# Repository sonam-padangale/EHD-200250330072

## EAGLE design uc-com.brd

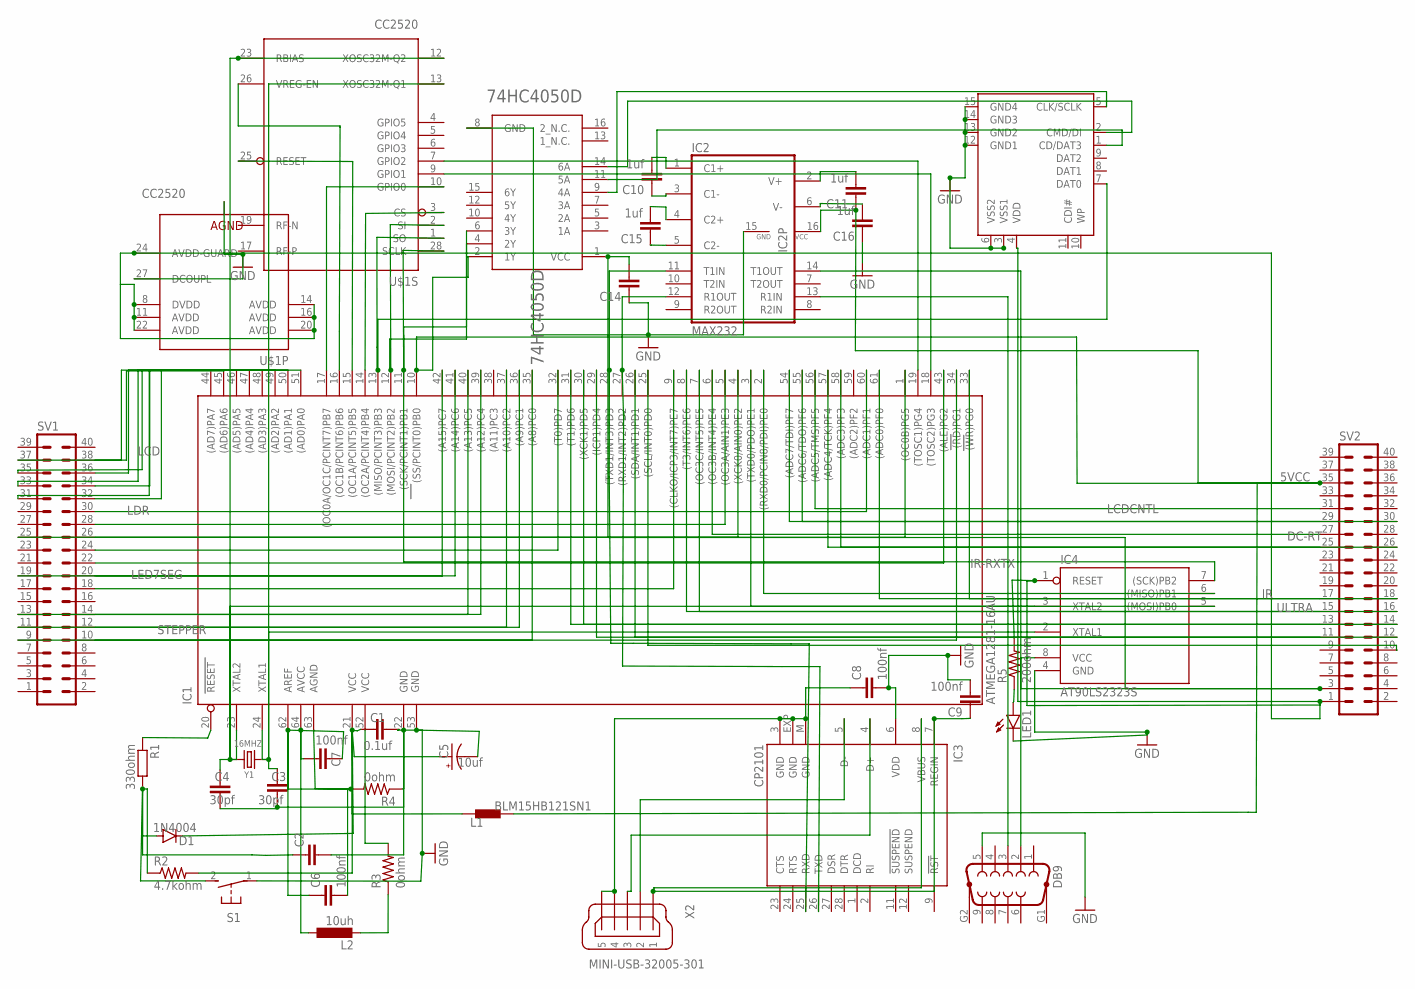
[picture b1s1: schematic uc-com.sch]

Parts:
74HC4050D: NXP_74HC4050DNXP_74HC4050D_0_0; NXP_74HC4050D_0
C1: 0.1uf; C0201
C2: C-EUC0402; C0402
C3, C4: 30pf; C0201
C5: 10uf; 085CS_1AR
C6, C7, C8, C9: 100nf; C0402K
C10, C11, C15, C16: 1uf; C0402K
C14: C-EUC0402K; C0402K
D1: 1N4004; DO41-10
DB9: F09HP-7.2
IC1: ATMEGA1281-16AU; TQFP64
IC2: MAX232; DIL16
IC3: CP2101; MLP28
IC4: AT90LS2323S; SO08
L1: BLM15HB121SN1; 0402
L2: 10uh; 0204/7
LED1: LED5MM
R1: 330ohm; R0603
R2: 4.7kohm; M0805
R3, R4: 0ohm; M0805
R5: 200ohm; M0805
S1: 31-XX; B3F-31XX
SDCARD: SDCARDVAR2; SDCMF-10915W010
SV1, SV2: 40P
U$1: CC2520; QFN50P500X500X100-29N
X2: MINI-USB-32005-301; 32005-301
Y1: 16MHZ; HC49US

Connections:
5VCC: 74HC4050D.2 (1Y), C11.1, IC1.10 ((SS/PCINT0)PB0), IC2.16 (VCC), L1.1, SV2.35
7SEG: IC1.41 ((A14)PC6), SV1.19
DC-RT: IC1.6 ((OC3B/INT4)PE4), SV2.27
DH: IC1.32 ((T0)PD7), SV1.24
GND: 74HC4050D.8 (GND), C1.2, C2.2, C3.2, C4.2, C5.-, C8.2, C9.2, C14.1, C16.1, DB9.5, IC1.22 (GND), IC1.53 (GND1), IC2.15 (GND), IC3.6 (VDD), IC4.4 (GND), LED1.K (C), R4.1, S1.1, SDCARD.3 (VSS1), SDCARD.6 (VSS2), SDCARD.12 (GND1), SDCARD.13 (GND2), SDCARD.14 (GND3), SDCARD.15 (GND4), U$1.27 (DCOUPL), U$1.29 (AGND)
IR: IC1.61 ((ADC0)PF0), SV2.17
IR-RXTX: IC1.33 ((WR)PG0), SV2.18
LCD: IC1.45 ((AD6)PA6), SV1.37
LCDCNTL: IC1.56 ((ADC5/TMS)PF5), SV2.31
LDR: IC1.60 ((ADC1)PF1), SV1.30
LED7SEG: IC1.43 ((ALE)PG2), SV1.22
unnamed: C2.1, D1.A, R1.2, R2.1, S1.2 (S)
unnamed: IC1.20 (RESET), R1.1
unnamed: C1.1, C5.+, D1.C, IC1.21 (VCC), L1.2, R2.2
unnamed: 74HC4050D.1 (VCC), C14.2, IC4.8 (VCC), SV2.3
unnamed: C4.1, IC1.23 (XTAL2), IC4.3 (XTAL2), U$1.12 (XOSC32M-Q2), U$1.23 (RBIAS), Y1.2
unnamed: C7.2, IC1.64 (AVCC), L2.1
unnamed: C3.1, IC1.24 (XTAL1), IC4.2 (XTAL1), U$1.13 (XOSC32M-Q1), Y1.1
unnamed: C6.1, C6.2, C7.1, IC1.62 (AREF), IC1.63 (AGND), R4.2
unnamed: IC1.27 ((RXD1/INT2)PD2), IC2.12 (R1OUT), IC3.26 (TXD)
unnamed: L2.2, R3.1
unnamed: IC1.52 (VCC1), R3.2
unnamed: IC1.28 ((TXD1/INT3)PD3), IC2.11 (T1IN), IC3.25 (RXD)
unnamed: IC1.44 ((AD7)PA7), SV1.38
unnamed: IC4.1 (RESET), R5.2, SDCARD.4 (VDD), SV2.1, U$1.8 (DVDD), U$1.11 (AVDD), U$1.14 (AVDD), U$1.16 (AVDD), U$1.20 (AVDD), U$1.22 (AVDD), U$1.24 (AVDD-GUARD)
unnamed: IC1.46 ((AD5)PA5), SV1.36
unnamed: IC1.47 ((AD4)PA4), SV1.35
unnamed: IC1.48 ((AD3)PA3), SV1.34
unnamed: IC1.49 ((AD2)PA2), SV1.33
unnamed: IC1.50 ((AD1)PA1), SV1.32
unnamed: IC1.51 ((AD0)PA0), SV1.31
unnamed: IC1.15 ((OC1A/PCINT5)PB5), U$1.25 (RESET)
unnamed: IC1.16 ((OC1B/PCINT6)PB6), U$1.26 (VREG-EN)
unnamed: 74HC4050D.6 (3Y), IC1.12 ((MOSI/PCINT2)PB2), U$1.2 (SI)
unnamed: IC1.13 ((MISO/PCINT3)PB3), SDCARD.7 (DAT0), U$1.1 (SO)
unnamed: 74HC4050D.4 (2Y), IC1.11 ((SCK/PCINT1)PB1), IC4.7 ((SCK)PB2), U$1.28 (SCLK)
unnamed: IC1.14 ((OC2A/PCINT4)PB4), U$1.3 (CS)
unnamed: IC1.17 ((OC0A/OC1C/PCINT7)PB7), U$1.10 (GPIO0)
unnamed: IC1.18 ((TOSC2)PG3), U$1.9 (GPIO1)
unnamed: IC1.19 ((TOSC1)PG4), U$1.7 (GPIO2)
unnamed: IC3.5 (D-), X2.2
unnamed: IC3.4 (D+), X2.3
unnamed: C9.1, IC3.7 (REGIN), IC3.8 (VBUS), X2.1
unnamed: C8.1, IC3.3 (GND), IC3.EXP (GND), IC3.M (GND), X2.4, X2.5
unnamed: DB9.3, IC2.13 (R1IN)
unnamed: DB9.2, IC2.14 (T1OUT)
unnamed: C15.1, IC2.5 (C2-)
unnamed: C15.2, IC2.4 (C2+)
unnamed: C11.2, IC2.2 (V+)
unnamed: C10.1, IC2.3 (C1-)
unnamed: C16.2, IC2.6 (V-)
unnamed: C10.2, IC2.1 (C1+)
unnamed: 74HC4050D.14 (6A), SDCARD.2 (CMD/DI)
unnamed: IC1.54 ((ADC7/TDI)PF7), SV2.29
unnamed: 74HC4050D.9 (4A), SDCARD.5 (CLK/SCLK)
unnamed: 74HC4050D.11 (5A), SDCARD.1 (CD/DAT3)
unnamed: IC1.55 ((ADC6/TDO)PF6), SV2.30
unnamed: LED1.A, R5.1
unnamed: IC1.42 ((A15)PC7), SV1.20
unnamed: IC1.58 ((ADC3)PF3), SV2.25
unnamed: IC1.57 ((ADC4/TCK)PF4), SV2.26
unnamed: IC1.1 ((OC0B)PG5), SV1.26
unnamed: IC1.4 ((XCK0/AIN0)PE2), SV1.25
unnamed: IC1.5 ((OC3A/AIN1)PE3), SV1.28
unnamed: IC1.7 ((OC3C/INT5)PE5), SV2.15
unnamed: IC1.25 ((SCL/INT0)PD0), SV2.10
unnamed: IC1.26 ((SDA/INT1)PD1), SV2.11
unnamed: IC1.29 ((ICP1)PD4), SV2.12
unnamed: IC1.30 ((XCK1)PD5), SV2.13
unnamed: IC1.31 ((T1)PD6), SV2.14
unnamed: IC1.35 ((A8)PC0), SV1.10
unnamed: IC1.39 ((A12)PC4), SV1.14
unnamed: IC1.36 ((A9)PC1), SV1.12
unnamed: IC1.37 ((A10)PC2), SV1.11
unnamed: IC1.40 ((A13)PC5), SV1.13
unnamed: IC1.9 ((CLKO/ICP3/INT7)PE7), SV1.18
unnamed: IC1.2 ((RXD0/PCIN8/PDI)PE0), IC4.6 ((MISO)PB1)
unnamed: IC1.3 ((TXD0/PDO)PE1), IC4.5 ((MOSI)PB0)
STEPPER: IC1.34 ((RD)PG1), SV1.9
ULTRA: IC1.8 ((T3/INT6)PE6), SV2.16

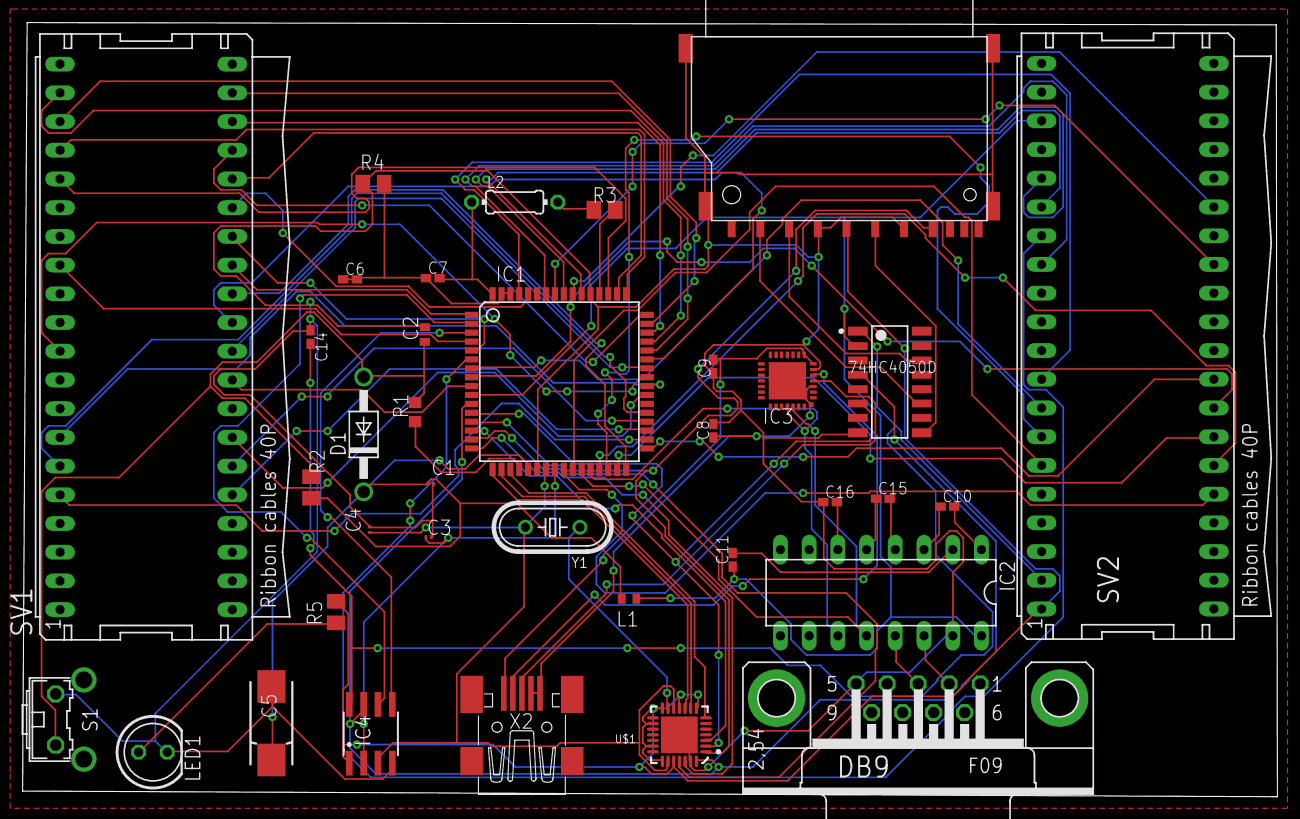
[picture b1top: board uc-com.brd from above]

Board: 2 copper layers, 111.0 x 68.5 mm, 36 parts (0 on the bottom side), 80 nets.

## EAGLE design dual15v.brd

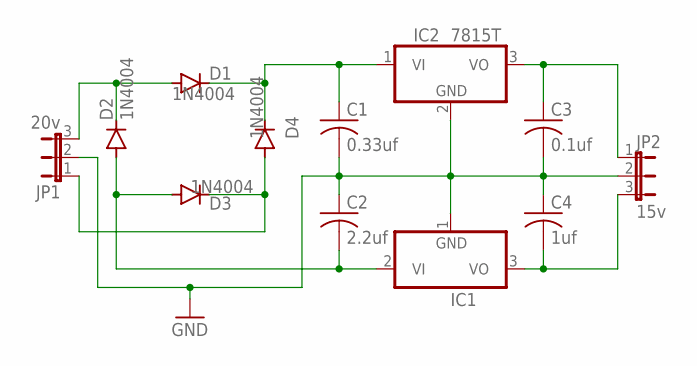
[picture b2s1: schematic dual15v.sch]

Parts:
C1: 0.33uf; C025-025X050
C2: 2.2uf; C025-025X050
C3: 0.1uf; C025-025X050
C4: 1uf; C025-025X050
D1, D2, D3, D4: 1N4004; DO41-10
IC1: 7915T; TO220H
IC2: 7815T; TO220H
JP1: 20v; JP2
JP2: 15v; JP2

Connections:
GND: C1.2, C2.1, C3.2, C4.1, IC1.1 (GND), IC2.2 (GND), JP1.2, JP2.2
unnamed: D1.A, D2.C, JP1.3
unnamed: C2.2, D2.A, D3.A, IC1.2 (VI)
unnamed: D3.C, D4.A, JP1.1
unnamed: C1.1, D1.C, D4.C, IC2.1 (VI)
unnamed: C4.2, IC1.3 (VO), JP2.3
unnamed: C3.1, IC2.3 (VO), JP2.1

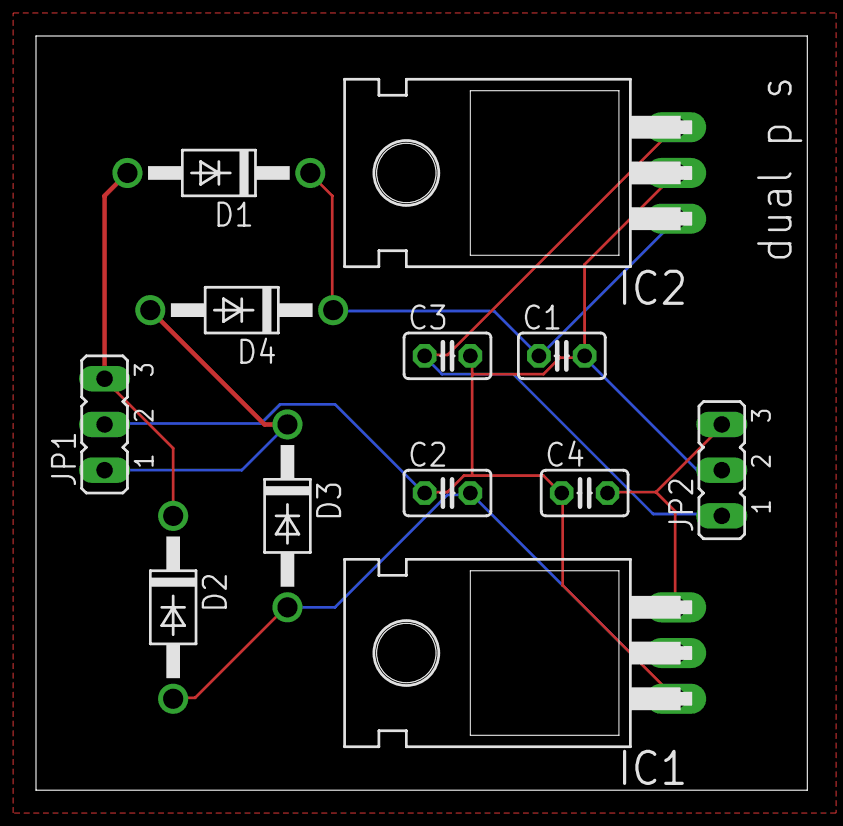
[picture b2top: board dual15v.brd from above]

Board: 2 copper layers, 42.8 x 41.9 mm, 12 parts (0 on the bottom side), 7 nets.

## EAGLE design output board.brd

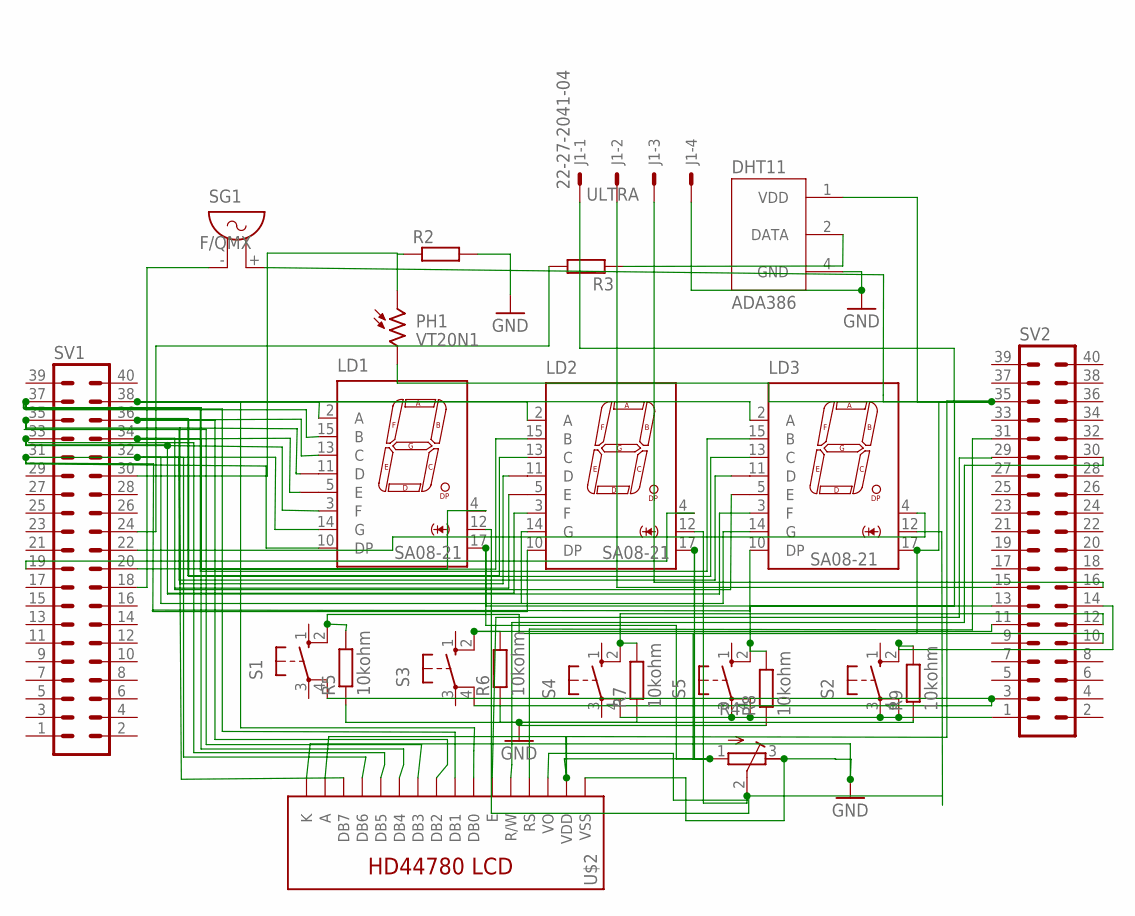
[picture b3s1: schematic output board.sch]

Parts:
DHT11: ADA386; XDCR_ADA386
J1: 22-27-2041-04; 6410-04
LD1, LD2, LD3: SA08-21
PH1: VT20N1; TO46-VT200
R2, R3: R-EU_M0805; M0805
R4: R-TRIMM3224J; RTRIM3224J
R5, R6, R7, R8, R9: 10kohm; R0201
S1, S2, S3, S4, S5: 10-XX; B3F-10XX
SG1: F/QMX
SV1, SV2: 40P
U$2: LCD-HD447803-HOLES16X2-3-HOLES; LCD-16X2-3HOLES

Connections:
GND: DHT11.4 (GND), J1.4, R2.2, R4.3 (E), R5.1, R6.1, R7.1, R8.1, R9.1, U$2.1 (VSS), U$2.16 (K)
unnamed: DHT11.2 (DATA), R3.1
unnamed: LD1.2 (A), LD2.2 (A), LD3.2 (A), SV1.38, U$2.7 (DB0)
unnamed: LD1.15 (B), LD2.15 (B), LD3.15 (B), SV1.37, U$2.8 (DB1)
unnamed: LD1.13 (C), LD2.13 (C), LD3.13 (C), SV1.36, U$2.9 (DB2)
unnamed: LD1.9 (D), LD2.9 (D), LD3.9 (D), SV1.35
unnamed: LD1.7 (E), LD2.7 (E), LD3.7 (E), SV1.34, U$2.11 (DB4)
unnamed: LD1.3 (F), LD2.3 (F), LD3.3 (F), SV1.33
unnamed: LD1.14 (G), LD2.14 (G), LD3.14 (G), SV1.32, U$2.13 (DB6)
unnamed: LD1.10 (DP), LD2.10 (DP), LD3.10 (DP), SV1.31, U$2.14 (DB7)
unnamed: SV2.29, U$2.6 (E)
unnamed: SV2.30, U$2.5 (R/W)
unnamed: SV2.31, U$2.4 (RS)
unnamed: LD1.12 (AN), LD2.12 (AN), LD3.12 (AN), R4.2 (S), U$2.3 (VO)
unnamed: PH1.1, R2.1
unnamed: R5.2, S1.2 (S1), SV2.10
unnamed: R6.2, S3.2 (S1), SV2.11
unnamed: R7.2, S4.2 (S1), SV2.12
unnamed: LD1.4 (AN), SV1.20
unnamed: LD2.4 (AN), SV1.19
unnamed: LD3.4 (AN), SV1.22
unnamed: R8.2, S5.2 (S1), SV2.13
unnamed: R9.2, S2.2 (S1), SV2.14
unnamed: S1.4 (P1), S3.4 (P1), SV2.3
unnamed: S2.3, S2.4 (P1), S4.4 (P1), S5.3, S5.4 (P1), SV2.1
unnamed: R3.2, SV1.24
unnamed: J1.2, SV2.15
unnamed: SG1.- (1), SV1.18
unnamed: J1.3, SV2.16
ULTRA: DHT11.1 (VDD), J1.1, LD1.17 (AN), LD2.17 (AN), LD3.17 (AN), PH1.2, R4.1 (A), SG1.+ (2), SV2.35, U$2.2 (VDD), U$2.15 (A)

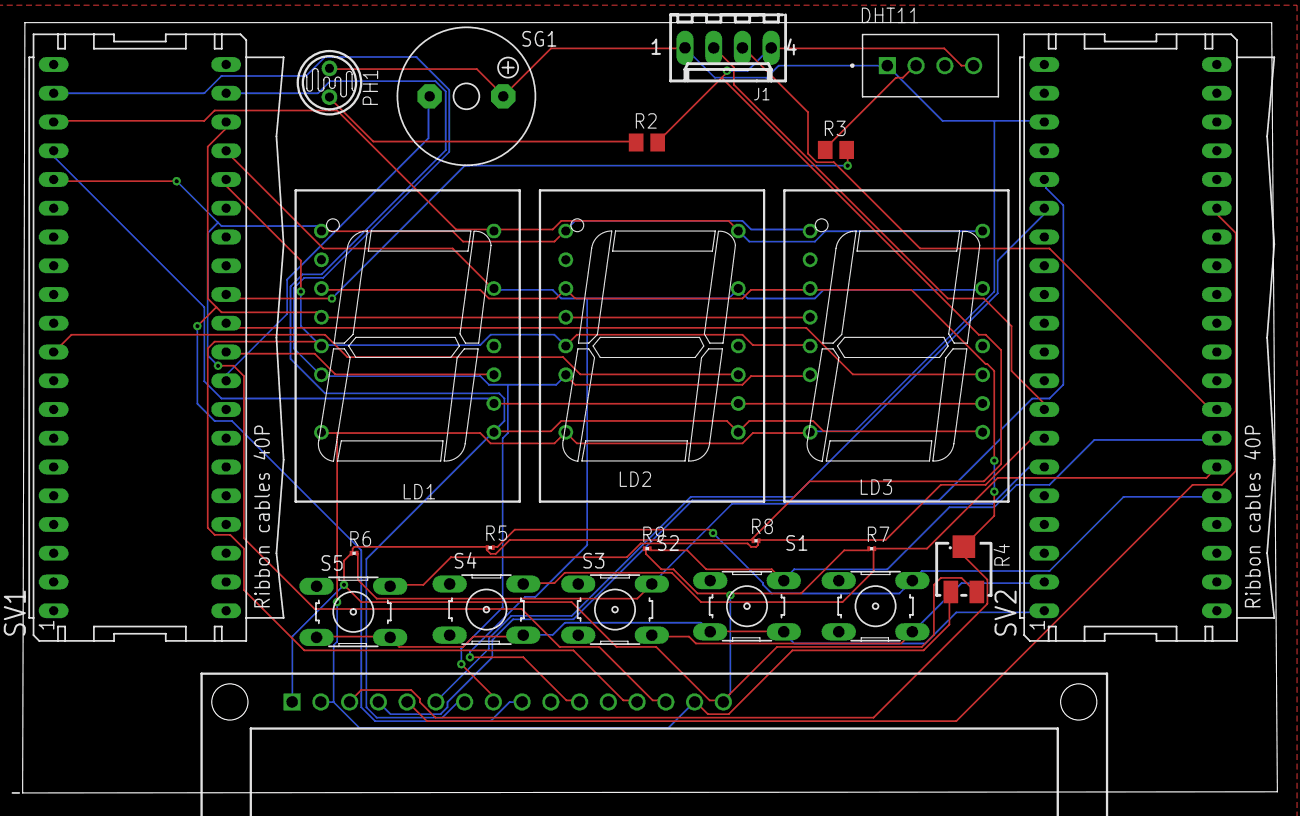
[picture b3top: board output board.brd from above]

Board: 2 copper layers, 110.9 x 68.1 mm, 23 parts (0 on the bottom side), 30 nets.

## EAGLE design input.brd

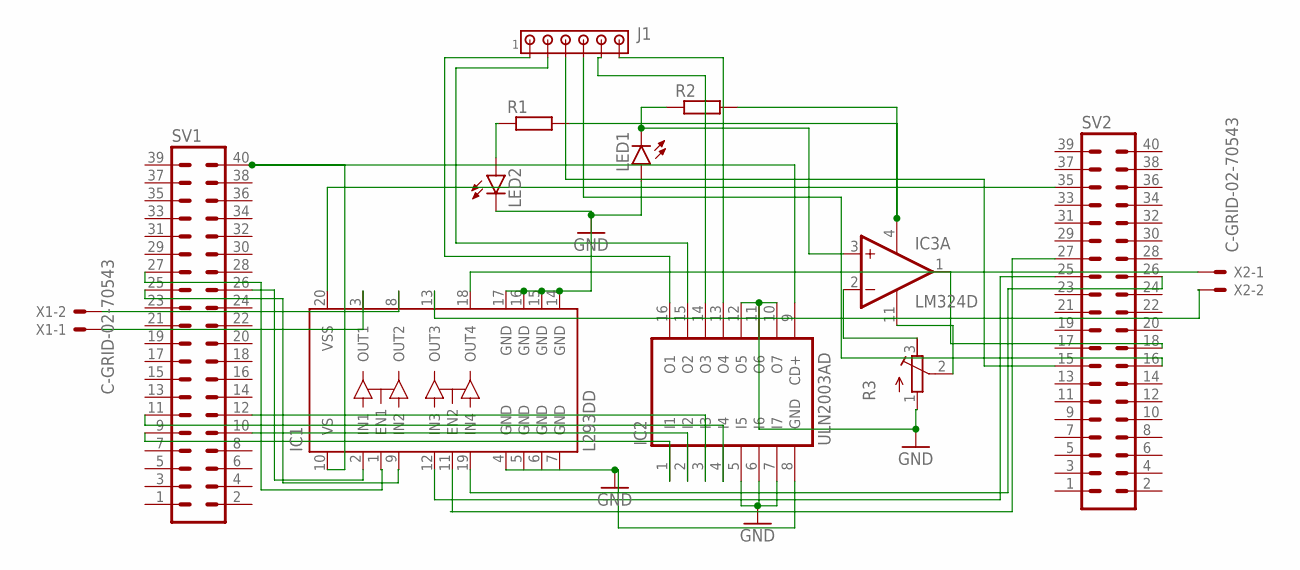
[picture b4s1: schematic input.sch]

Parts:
IC1: L293DD; SO20
IC2: ULN2003AD; SO16
IC3: LM324D; SO14
J1: MTA06-100; 10X06MTA
LED1, LED2: LED5MM
R1, R2: R-EU_R0201; R0201
R3: R-TRIMM3103; RTRIM3103
SV1, SV2: 40P
X1, X2: C-GRID-02-70543; 70543-02

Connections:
GND: IC1.4 (GND), IC1.5 (GND), IC1.6 (GND), IC1.7 (GND), IC1.14 (GND), IC1.15 (GND), IC1.16 (GND), IC1.17 (GND), IC2.5 (I5), IC2.6 (I6), IC2.7 (I7), IC2.8 (GND), IC2.10 (O7), IC2.11 (O6), IC2.12 (O5), LED1.A, LED2.K (C), R3.1 (A)
unnamed: IC3.3 (+IN), LED1.K (C), R2.1
unnamed: LED2.A, R1.1
unnamed: IC3.11 (V-), R3.2 (S)
unnamed: IC3.2 (-IN), R3.3 (E)
unnamed: IC2.1 (I1), SV1.9
unnamed: IC2.2 (I2), SV1.10
unnamed: IC2.3 (I3), SV1.12
unnamed: IC1.2 (IN1), SV1.26
unnamed: IC1.9 (IN2), SV1.25
unnamed: IC1.1 (EN1), SV1.27
unnamed: IC1.12 (IN3), SV2.25
unnamed: IC1.19 (IN4), SV2.26
unnamed: IC1.11 (EN2), SV2.27
unnamed: IC1.3 (OUT1), X1.1
unnamed: IC1.8 (OUT2), X1.2
unnamed: IC1.10 (VS), IC2.9 (CD+), SV1.40
unnamed: IC1.20 (VSS), SV2.35
unnamed: IC2.4 (I4), SV1.11
unnamed: IC1.18 (OUT4), X2.1
unnamed: IC1.13 (OUT3), X2.2
unnamed: IC2.16 (O1), J1.1
unnamed: IC2.15 (O2), J1.2
unnamed: IC2.14 (O3), J1.5
unnamed: IC2.13 (O4), J1.6
unnamed: IC3.4 (V+), R1.2, R2.2
unnamed: IC3.1 (OUT), SV2.18
unnamed: J1.3, SV2.15
unnamed: J1.4, SV2.16

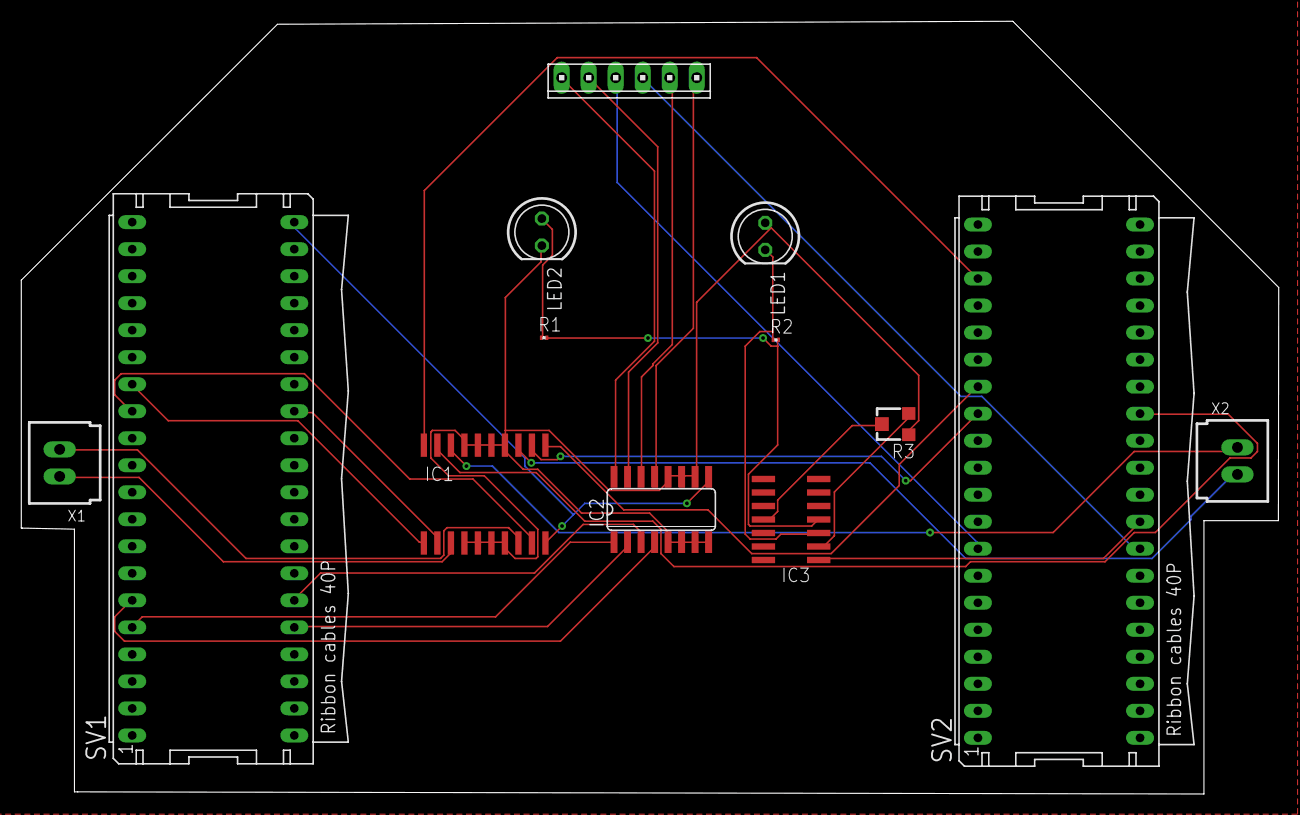
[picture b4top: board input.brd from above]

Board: 2 copper layers, 118.2 x 72.7 mm, 13 parts (0 on the bottom side), 29 nets.

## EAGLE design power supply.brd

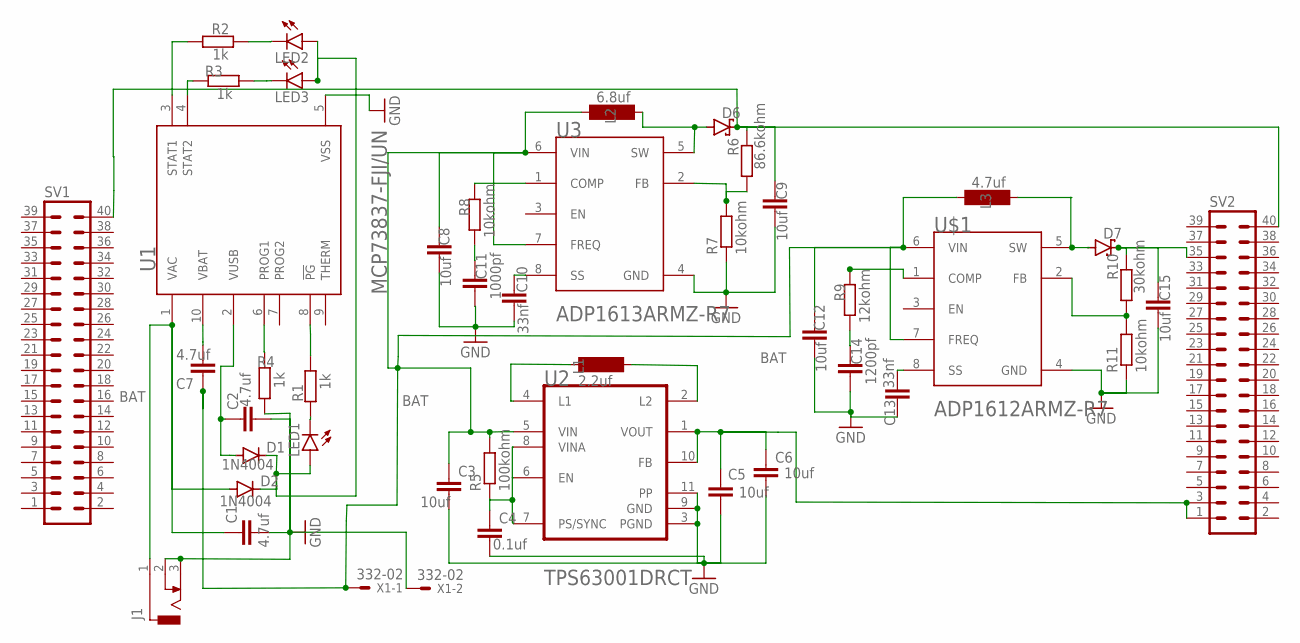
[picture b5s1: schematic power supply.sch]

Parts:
C1, C2, C7: 4.7uf; C025-024X044
C3, C5, C6, C8, C9, C12, C15: 10uf; C0201
C4: 0.1uf; C0201
C10, C13: 33nf; C0201
C11: 1000pf; C0201
C14: 1200pf; C0201
D1, D2: 1N4004; DO41-10
D6, D7: P4KEXX; DO41-10
J1: DCJ0303
L1: 2.2uf; SD75
L2: 6.8uf; SD75
L3: 4.7uf; SD75
LED1, LED2, LED3: LED; SMARTLED-TTW
R1, R2, R3, R4: 1k; R01005
R5: 100kohm; R01005
R6: 86.6kohm; R01005
R7, R8, R11: 10kohm; R01005
R9: 12kohm; R01005
R10: 30kohm; R01005
SV1, SV2: 40P
U1: MICROCHIP_MCP73837-FJI-UNMICROCHIP_MCP73837-FJI-U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; MICROCHIP_MCP73837-FJI-UN_0
U2: TEXAS_INSTRUMENTS_TPS63001DRCTTEXAS_INSTRUMENTS_T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; TEXAS_INSTRUMENTS_TPS63001DRCT_0
U3: ANALOG_DEVICES_INC_ADP1613ARMZ-R7ANALOG_DEVICES_I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; ANALOG_DEVICES_INC_ADP1613ARMZ-R7_0
U$1: ADP1612
X1: 332-02

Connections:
BAT: C3.1, C7.1, C8.1, C12.1, L2.1, L3.1, R5.2, U2.5 (VIN), U3.6 (VIN), U3.7 (FREQ), U$1.6 (VIN), U$1.7 (FREQ), X1.1
BATCHARGEER: D1.C, D2.C, LED1.A@1 (A), LED2.A@1 (A), LED3.A@1 (A)
GND: C1.2, C2.2, C3.2, C4.2, C5.2, C6.2, C8.2, C9.2, C10.2, C11.2, C12.2, C13.1, C14.2, C15.2, J1.2, J1.3, R4.1, R7.1, R11.1, U1.5 (VSS), U2.3 (PGND), U2.9 (GND), U2.11 (PP), U3.4 (GND), U$1.4 (GND), X1.2
unnamed: C1.1, D2.A, J1.1, U1.1 (VAC)
unnamed: C2.1, D1.A, U1.2 (VUSB)
unnamed: R3.1, U1.4 (STAT2)
unnamed: LED2.C@1 (C), R2.2
unnamed: R4.2, U1.6 (PROG1)
unnamed: R1.2, U1.8 (!PG!)
unnamed: LED1.C@1 (C), R1.1
unnamed: LED3.C@1 (C), R3.2
unnamed: R2.1, U1.3 (STAT1)
unnamed: C13.2, U$1.8 (SS)
unnamed: C7.2, U1.10 (VBAT)
unnamed: R9.2, U$1.1 (COMP)
unnamed: C4.1, R5.1, U2.6 (EN), U2.7 (PS/SYNC), U2.8 (VINA)
unnamed: C14.1, R9.1
unnamed: L1.1, U2.4 (L1)
unnamed: L1.2, U2.2 (L2)
unnamed: C5.1, C6.1, SV2.1, SV2.3, U2.1 (VOUT), U2.10 (FB)
unnamed: R8.2, U3.1 (COMP)
unnamed: C10.1, U3.8 (SS)
unnamed: C9.1, D6.C, R6.2, SV1.40, SV2.40
unnamed: R6.1, R7.2, U3.2 (FB)
unnamed: C11.1, R8.1
unnamed: C15.1, D7.C, R10.2, SV2.35
unnamed: D7.A, U$1.5 (SW)
unnamed: R10.1, R11.2, U$1.2 (FB)
unnamed: D6.A, L2.2, U3.5 (SW)

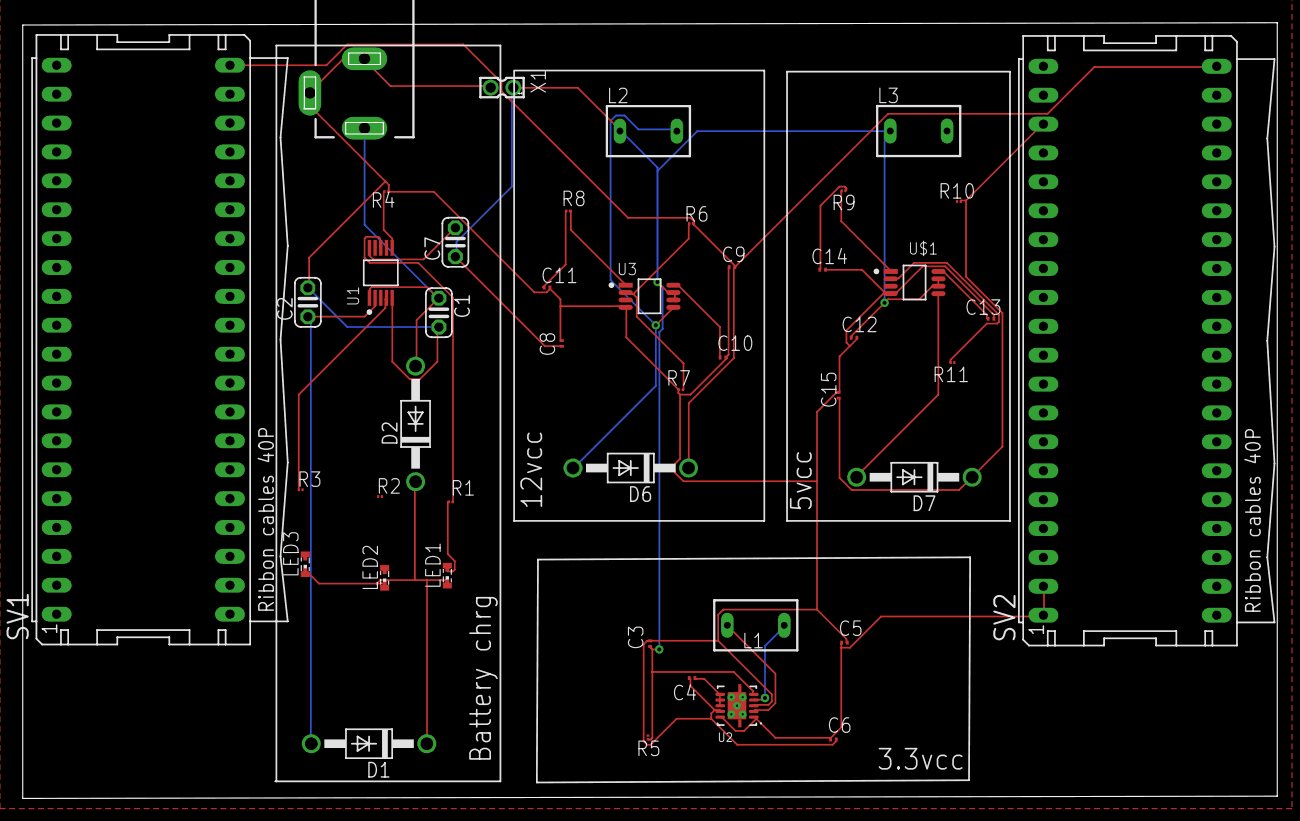
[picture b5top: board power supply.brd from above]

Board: 2 copper layers, 110.3 x 68.2 mm, 44 parts (0 on the bottom side), 29 nets.

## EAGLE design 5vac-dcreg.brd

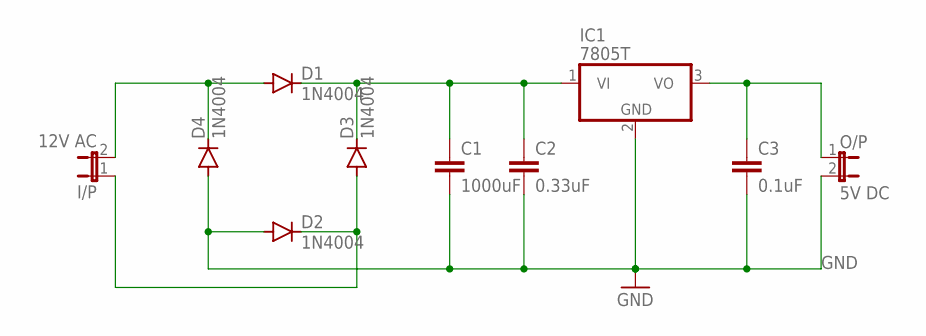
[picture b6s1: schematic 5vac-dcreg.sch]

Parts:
C1: 1000uF; C2.5-3
C2: 0.33uF; C2.5-3
C3: 0.1uF; C2.5-3
D1, D2, D3, D4: 1N4004; DO41-10
I/P: 12V AC; JP1
IC1: 7805T; TO220H
O/P: 5V DC; JP1

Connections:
GND: C1.2, C2.2, C3.2, D2.A, D4.A, IC1.2 (GND), O/P.2
unnamed: D2.C, D3.A, I/P.1
unnamed: C1.1, C2.1, D1.C, D3.C, IC1.1 (VI)
unnamed: D1.A, D4.C, I/P.2
unnamed: C3.1, IC1.3 (VO), O/P.1

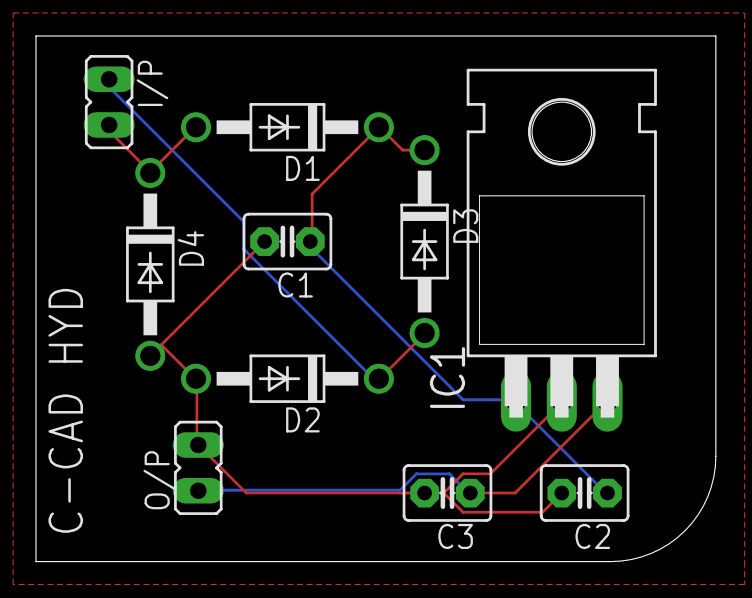
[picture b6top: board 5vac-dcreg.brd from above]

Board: 2 copper layers, 37.8 x 29.2 mm, 10 parts (0 on the bottom side), 5 nets.
